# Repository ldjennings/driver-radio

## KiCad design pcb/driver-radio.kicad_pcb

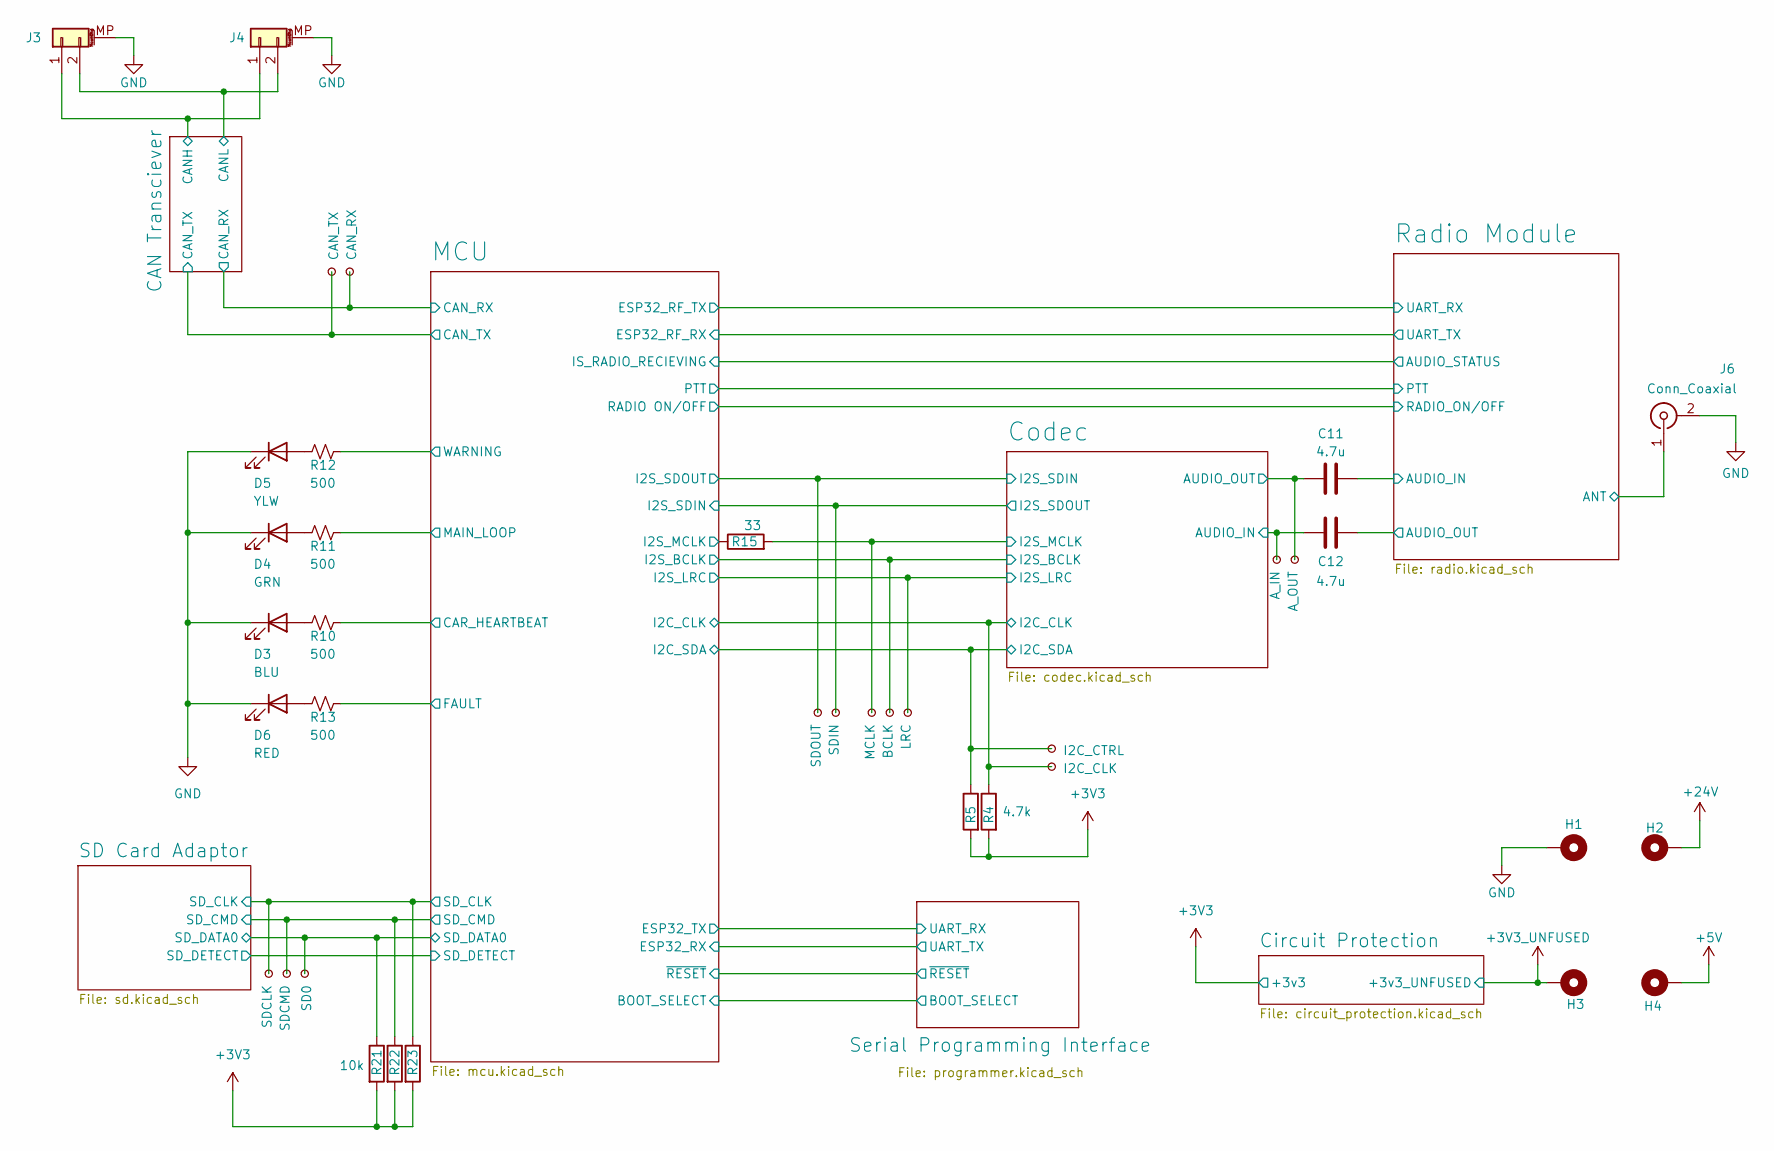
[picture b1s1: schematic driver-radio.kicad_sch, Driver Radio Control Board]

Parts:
C11, C12: 4.7u; C_0805_2012Metric
D3: BLU; LED_0402_1005Metric
D4: GRN; LED_0402_1005Metric
D5: YLW; LED_0402_1005Metric
D6: RED; LED_0402_1005Metric
H1, H2, H3, H4: MountingHole_Pad; glv_mainboard_hole
J3, J4: Conn_01x02_MountingPin; JST_GH_SM02B-GHS-TB_1x02-1MP_P1.25mm_Horizontal
J6: Conn_Coaxial; SMA_Molex_73251-1153_EdgeMount_Horizontal
R4, R5: 4.7k; R_0402_1005Metric
R10, R11, R12, R13: 500; R_0402_1005Metric
R15: 33; R_0402_1005Metric
R21, R22, R23: 10k; R_0402_1005Metric_Pad0.72x0.64mm_HandSolder
TP1: CAN_TX; tp-ev24-nobacksilk
TP2: CAN_RX; tp-ev24-nobacksilk
TP3: I2C_CTRL; tp-ev24-nobacksilk
TP4: I2C_CLK; tp-ev24-nobacksilk
TP5: MCLK; tp-ev24-nobacksilk
TP6: LRC; tp-ev24-nobacksilk
TP7: BCLK; tp-ev24-nobacksilk
TP8: SDIN; tp-ev24-nobacksilk
TP9: SDOUT; tp-ev24-nobacksilk
TP10: A_OUT; tp-ev24-nobacksilk
TP11: A_IN; tp-ev24-nobacksilk
TP12: SD0; tp-ev24-nobacksilk
TP16: SDCLK; tp-ev24-nobacksilk
TP17: SDCMD; tp-ev24-nobacksilk

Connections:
+3V3: R4.2, R5.2, R21.2, R22.2, R23.2; also elsewhere on the board
+3V3_UNFUSED: H3.1; also elsewhere on the board
+5V: H4.1; also elsewhere on the board
+24V: H2.1
/CAN Transciever/CANH: J3.1, J4.1; also elsewhere on the board
/CAN Transciever/CANL: J3.2, J4.2; also elsewhere on the board
/CAN Transciever/CAN_RX: TP2.1; also elsewhere on the board
/CAN Transciever/CAN_TX: TP1.1; also elsewhere on the board
/Codec/AUDIO_IN: C12.2, TP11.1; also elsewhere on the board
/Codec/AUDIO_OUT: C11.2, TP10.1; also elsewhere on the board
/Codec/I2C_CLK: R4.1, TP4.1; also elsewhere on the board
/Codec/I2C_SDA: R5.1, TP3.1; also elsewhere on the board
/Codec/I2S_BCLK: TP7.1; also elsewhere on the board
/Codec/I2S_LRC: TP6.1; also elsewhere on the board
/Codec/I2S_MCLK: R15.2, TP5.1; also elsewhere on the board
/Codec/I2S_SDIN: TP9.1; also elsewhere on the board
/Codec/I2S_SDOUT: TP8.1; also elsewhere on the board
/MCU/BOOT_SELECT: R15.1; also elsewhere on the board
/MCU/CAR_HEARTBEAT: R10.1; also elsewhere on the board
/MCU/FAULT: R13.1; also elsewhere on the board
/MCU/MAIN_LOOP: R11.1; also elsewhere on the board
/MCU/SD_CLK: R23.1, TP16.1; also elsewhere on the board
/MCU/SD_CMD: R22.1, TP17.1; also elsewhere on the board
/MCU/SD_DATA0: R21.1, TP12.1; also elsewhere on the board
/MCU/WARNING: R12.1; also elsewhere on the board
/Radio Module/ANT: J6.1 (In); also elsewhere on the board
/Radio Module/AUDIO_IN: C11.1; also elsewhere on the board
/Radio Module/AUDIO_OUT: C12.1; also elsewhere on the board
GND: D3.1 (K), D4.1 (K), D5.1 (K), D6.1 (K), H1.1, J3.MP (MountPin), J4.MP (MountPin), J6.2 (Ext); also elsewhere on the board
unnamed: D3.2 (A), R10.2
unnamed: D4.2 (A), R11.2
unnamed: D5.2 (A), R12.2
unnamed: D6.2 (A), R13.2

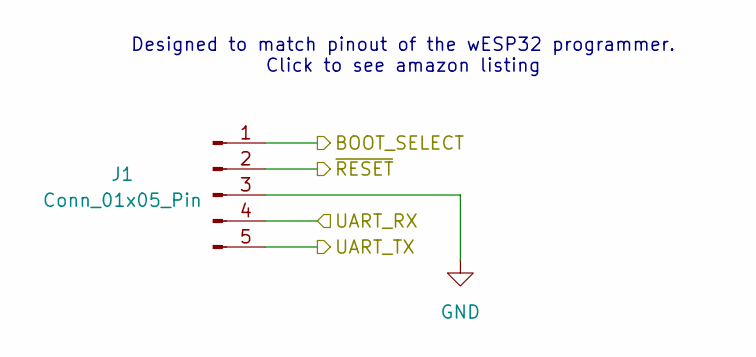
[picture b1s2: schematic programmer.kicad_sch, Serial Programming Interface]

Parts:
J1: Conn_01x05_Pin; PinHeader_1x05_P2.54mm_Vertical

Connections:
/MCU/BOOT_SELECT: J1.1; also elsewhere on the board
/MCU/ESP32_RX: J1.5; also elsewhere on the board
/MCU/ESP32_TX: J1.4; also elsewhere on the board
/MCU/~RESET: J1.2; also elsewhere on the board
GND: J1.3; also elsewhere on the board

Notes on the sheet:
Designed to match pinout of the wESP32 programmer. Click to see amazon listing

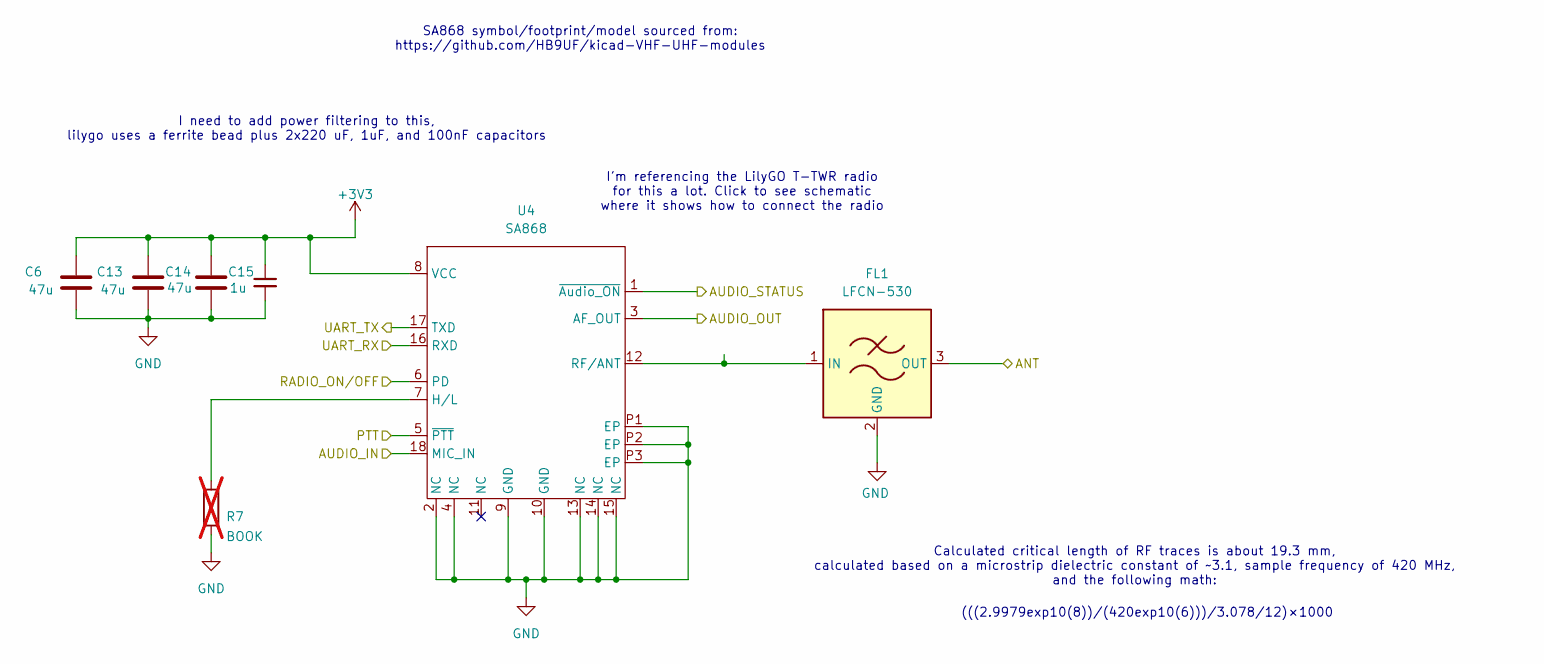
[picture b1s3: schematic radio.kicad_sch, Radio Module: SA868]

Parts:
C6, C13, C14: 47u; C_1206_3216Metric
C15: 1u; C_0402_1005Metric
FL1: LFCN-530; Filter_Mini-Circuits_FV1206
R7: BOOK; R_0402_1005Metric; not fitted
U4: SA868; VHF_UHF_Module_generic

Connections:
+3V3: C6.1, C13.1, C14.1, C15.1, U4.8 (VCC); also elsewhere on the board
/MCU/ESP32_RF_RX: U4.17 (TXD); also elsewhere on the board
/MCU/ESP32_RF_TX: U4.16 (RXD); also elsewhere on the board
/MCU/IS_RADIO_RECIEVING: U4.1 (~Audio_ON); also elsewhere on the board
/MCU/PTT: U4.5 (~PTT); also elsewhere on the board
/MCU/RADIO ON/OFF: U4.6 (PD); also elsewhere on the board
/Radio Module/ANT: FL1.3 (OUT); also elsewhere on the board
/Radio Module/AUDIO_IN: U4.18 (MIC_IN); also elsewhere on the board
/Radio Module/AUDIO_OUT: U4.3 (AF_OUT); also elsewhere on the board
GND: C6.2, C13.2, C14.2, C15.2, FL1.2 (GND), FL1.4 (GND), R7.1, U4.2 (NC), U4.4 (NC), U4.9 (GND), U4.10 (GND), U4.13 (NC), U4.14 (NC), U4.15 (NC), U4.P1 (EP), U4.P2 (EP), U4.P3 (EP); also elsewhere on the board
unnamed: FL1.1 (IN), U4.12 (RF/ANT)
unnamed: R7.2, U4.7 (H/L)

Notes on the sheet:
I'm referencing the LilyGO T-TWR radio for this a lot. Click to see schematic where it shows how to connect the radio
SA868 symbol/footprint/model sourced from: https://github.com/HB9UF/kicad-VHF-UHF-modules
I need to add power filtering to this, lilygo uses a ferrite bead plus 2x220 uF, 1uF, and 100nF capacitors
Calculated critical length of RF traces is about 19.3 mm, calculated based on a microstrip dielectric constant of ~3.1, sample frequency of 420 MHz, and the following math:
(((2.9979exp10(8))/(420exp10(6)))/3.078/12)×1000

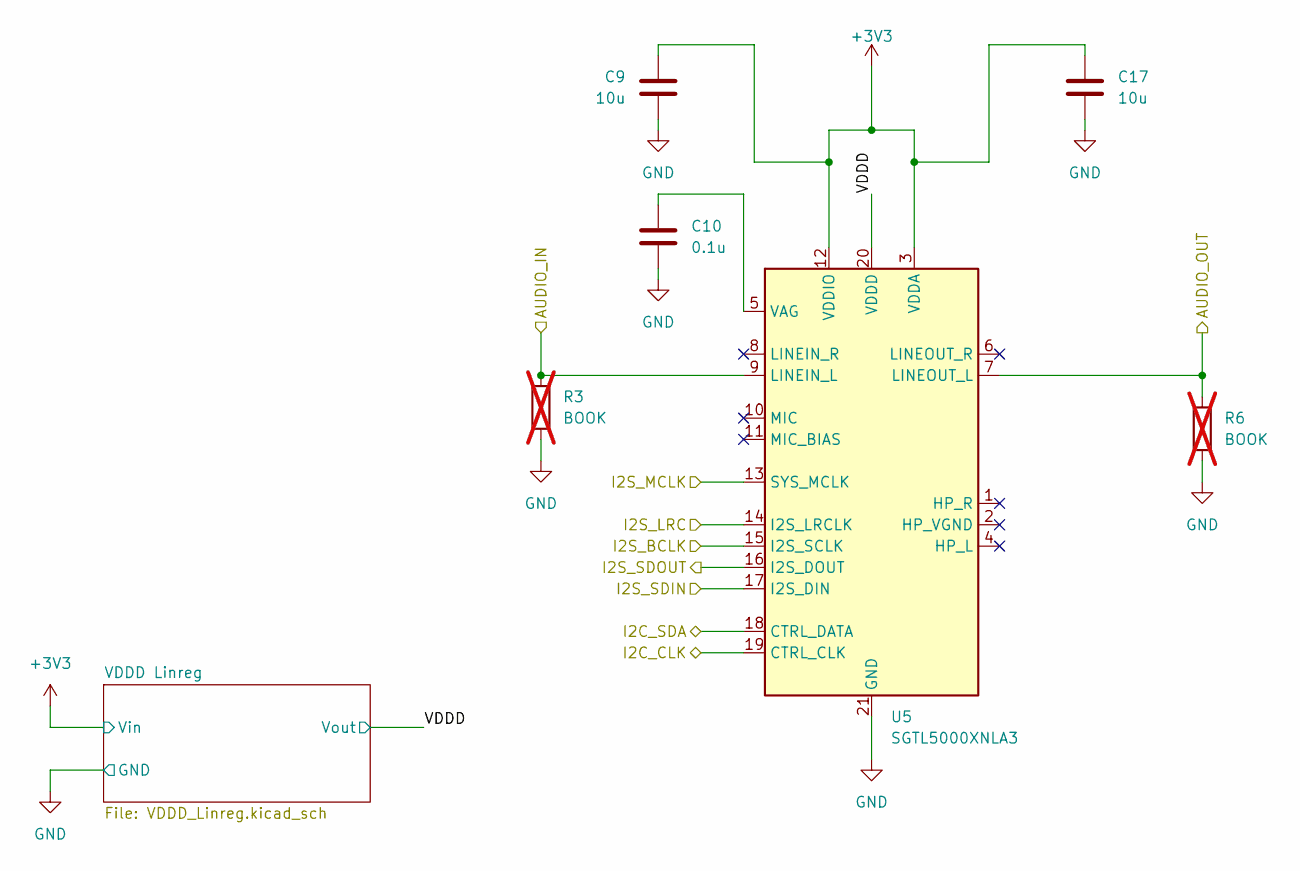
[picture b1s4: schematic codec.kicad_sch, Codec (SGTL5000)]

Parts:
C9, C17: 10u; C_0402_1005Metric
C10: 0.1u; C_0402_1005Metric
R3, R6: BOOK; R_0402_1005Metric; not fitted
U5: SGTL5000XNLA3; QFN-20-1EP_3x3mm_P0.4mm_EP1.65x1.65mm

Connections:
+3V3: C9.1, C17.1, U5.3 (VDDA), U5.12 (VDDIO); also elsewhere on the board
/Codec/AUDIO_IN: R3.2, U5.9 (LINEIN_L); also elsewhere on the board
/Codec/AUDIO_OUT: R6.2, U5.7 (LINEOUT_L); also elsewhere on the board
/Codec/I2C_CLK: U5.19 (CTRL_CLK); also elsewhere on the board
/Codec/I2C_SDA: U5.18 (CTRL_DATA); also elsewhere on the board
/Codec/I2S_BCLK: U5.15 (I2S_SCLK); also elsewhere on the board
/Codec/I2S_LRC: U5.14 (I2S_LRCLK); also elsewhere on the board
/Codec/I2S_MCLK: U5.13 (SYS_MCLK); also elsewhere on the board
/Codec/I2S_SDIN: U5.17 (I2S_DIN); also elsewhere on the board
/Codec/I2S_SDOUT: U5.16 (I2S_DOUT); also elsewhere on the board
/Codec/VDDD: U5.20 (VDDD); also elsewhere on the board
GND: C9.2, C10.2, C17.2, R3.1, R6.1, U5.21 (GND); also elsewhere on the board
unnamed: C10.1, U5.5 (VAG)

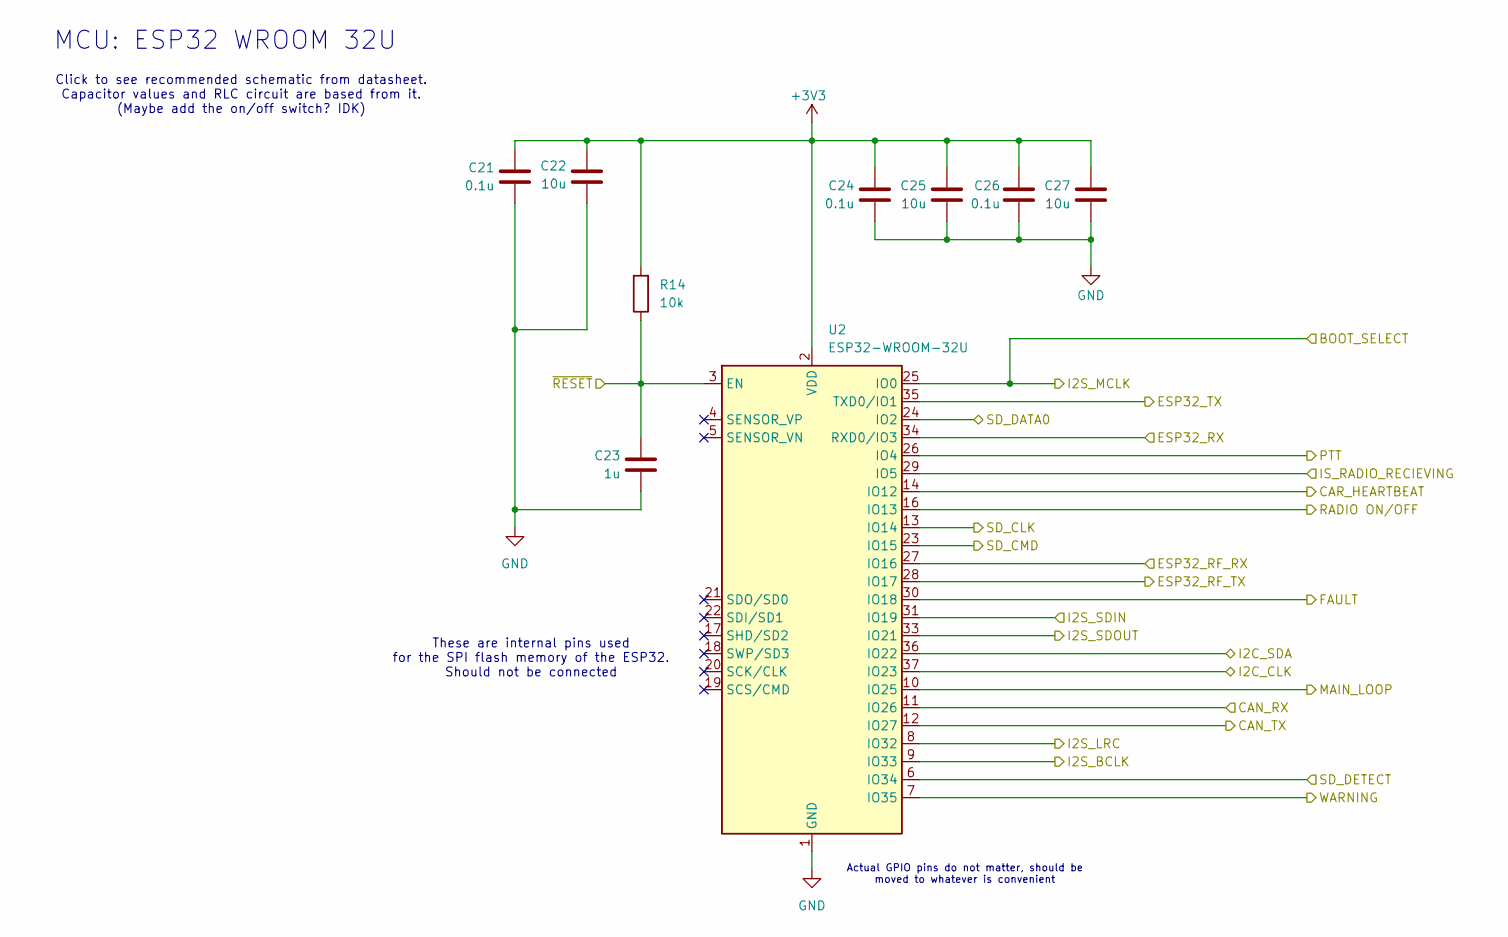
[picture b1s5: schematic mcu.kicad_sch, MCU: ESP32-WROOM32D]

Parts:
C21, C24, C26: 0.1u; C_0402_1005Metric
C22, C25, C27: 10u; C_0402_1005Metric
C23: 1u; C_0402_1005Metric
R14: 10k; R_0402_1005Metric
U2: ESP32-WROOM-32U

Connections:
+3V3: C21.1, C22.1, C24.1, C25.1, C26.1, C27.1, R14.2, U2.2 (VDD); also elsewhere on the board
/CAN Transciever/CAN_RX: U2.11 (IO26); also elsewhere on the board
/CAN Transciever/CAN_TX: U2.12 (IO27); also elsewhere on the board
/Codec/I2C_CLK: U2.37 (IO23); also elsewhere on the board
/Codec/I2C_SDA: U2.36 (IO22); also elsewhere on the board
/Codec/I2S_BCLK: U2.9 (IO33); also elsewhere on the board
/Codec/I2S_LRC: U2.8 (IO32); also elsewhere on the board
/Codec/I2S_SDIN: U2.33 (IO21); also elsewhere on the board
/Codec/I2S_SDOUT: U2.31 (IO19); also elsewhere on the board
/MCU/BOOT_SELECT: U2.25 (IO0); also elsewhere on the board
/MCU/CAR_HEARTBEAT: U2.14 (IO12); also elsewhere on the board
/MCU/ESP32_RF_RX: U2.27 (IO16); also elsewhere on the board
/MCU/ESP32_RF_TX: U2.28 (IO17); also elsewhere on the board
/MCU/ESP32_RX: U2.34 (RXD0/IO3); also elsewhere on the board
/MCU/ESP32_TX: U2.35 (TXD0/IO1); also elsewhere on the board
/MCU/FAULT: U2.30 (IO18); also elsewhere on the board
/MCU/IS_RADIO_RECIEVING: U2.29 (IO5); also elsewhere on the board
/MCU/MAIN_LOOP: U2.10 (IO25); also elsewhere on the board
/MCU/PTT: U2.26 (IO4); also elsewhere on the board
/MCU/RADIO ON/OFF: U2.16 (IO13); also elsewhere on the board
/MCU/SD_CLK: U2.13 (IO14); also elsewhere on the board
/MCU/SD_CMD: U2.23 (IO15); also elsewhere on the board
/MCU/SD_DATA0: U2.24 (IO2); also elsewhere on the board
/MCU/SD_DETECT: U2.6 (IO34); also elsewhere on the board
/MCU/WARNING: U2.7 (IO35); also elsewhere on the board
/MCU/~RESET: C23.2, R14.1, U2.3 (EN); also elsewhere on the board
GND: C21.2, C22.2, C23.1, C24.2, C25.2, C26.2, C27.2, U2.1 (GND), U2.15 (GND), U2.38 (GND), U2.39 (GND); also elsewhere on the board

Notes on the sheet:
Actual GPIO pins do not matter, should be moved to whatever is convenient
Click to see recommended schematic from datasheet. Capacitor values and RLC circuit are based from it. (Maybe add the on/off switch? IDK)
These are internal pins used for the SPI flash memory of the ESP32. Should not be connected
MCU: ESP32 WROOM 32U

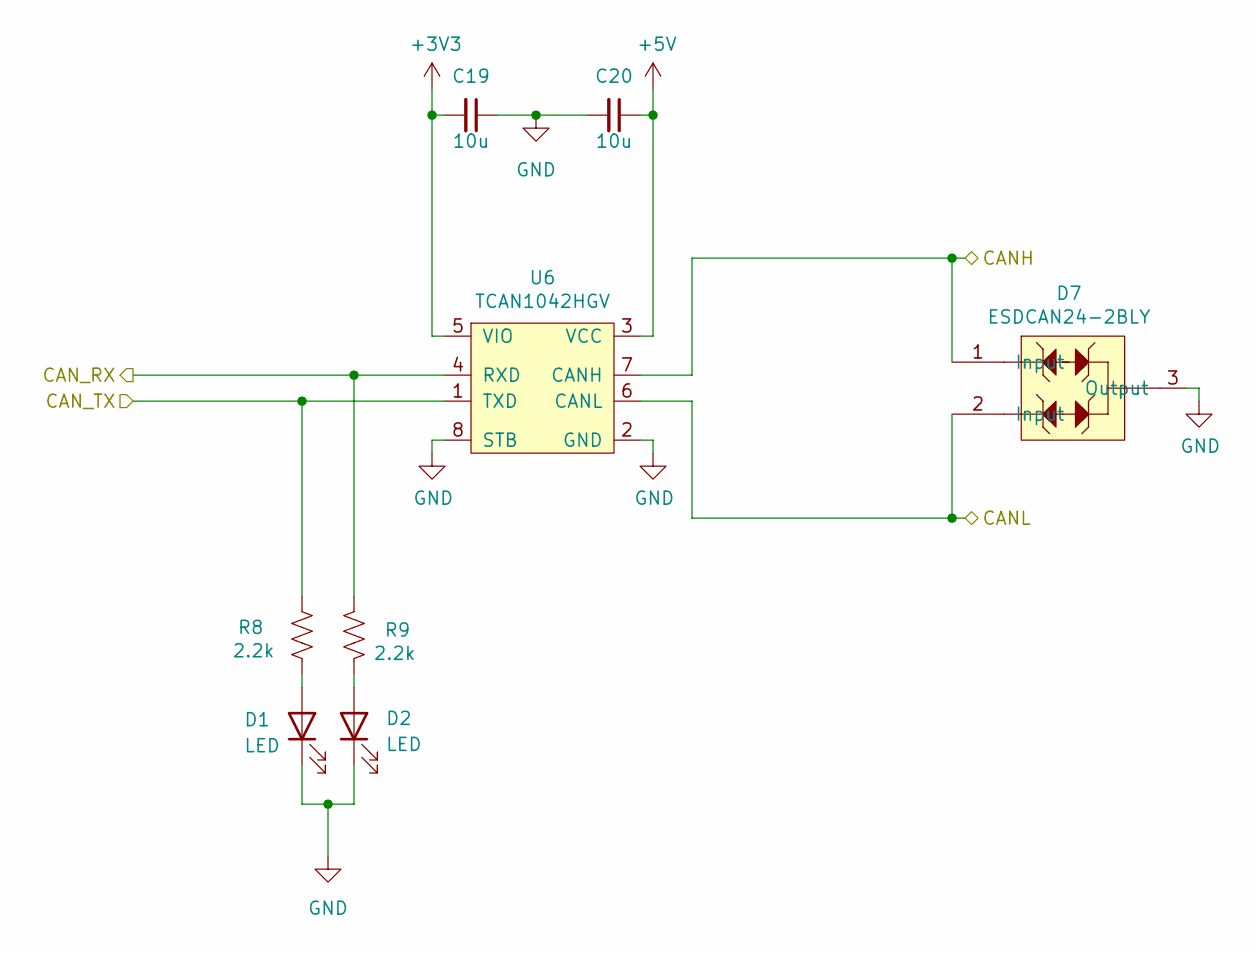
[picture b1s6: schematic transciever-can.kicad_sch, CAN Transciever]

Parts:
C19, C20: 10u; C_0402_1005Metric
D1, D2: LED; LED_0402_1005Metric
D7: ESDCAN24-2BLY; SOT-23-3
R8, R9: 2.2k; R_0402_1005Metric
U6: TCAN1042HGV; SOIC-8_3.9x4.9mm_P1.27mm

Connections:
+3V3: C19.2, U6.5 (VIO); also elsewhere on the board
+5V: C20.1, U6.3 (VCC); also elsewhere on the board
/CAN Transciever/CANH: D7.1 (Input), U6.7 (CANH); also elsewhere on the board
/CAN Transciever/CANL: D7.2 (Input), U6.6 (CANL); also elsewhere on the board
/CAN Transciever/CAN_RX: R9.1, U6.4 (RXD); also elsewhere on the board
/CAN Transciever/CAN_TX: R8.1, U6.1 (TXD); also elsewhere on the board
GND: C19.1, C20.2, D1.1 (K), D2.1 (K), D7.3 (Output), U6.2 (GND), U6.8 (STB); also elsewhere on the board
unnamed: D1.2 (A), R8.2
unnamed: D2.2 (A), R9.2

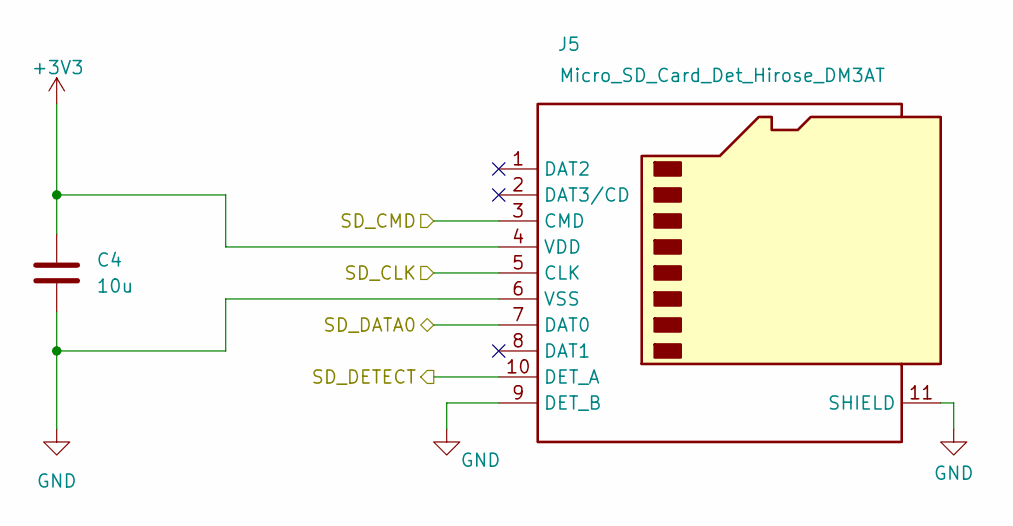
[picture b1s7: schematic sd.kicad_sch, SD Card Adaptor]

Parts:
C4: 10u; C_0402_1005Metric
J5: Micro_SD_Card_Det_Hirose_DM3AT; microSD_HC_Hirose_DM3BT-DSF-PEJS

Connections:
+3V3: C4.1, J5.4 (VDD); also elsewhere on the board
/MCU/SD_CLK: J5.5 (CLK); also elsewhere on the board
/MCU/SD_CMD: J5.3 (CMD); also elsewhere on the board
/MCU/SD_DATA0: J5.7 (DAT0); also elsewhere on the board
/MCU/SD_DETECT: J5.10 (DET_A); also elsewhere on the board
GND: C4.2, J5.6 (VSS), J5.9 (DET_B), J5.11 (SHIELD); also elsewhere on the board

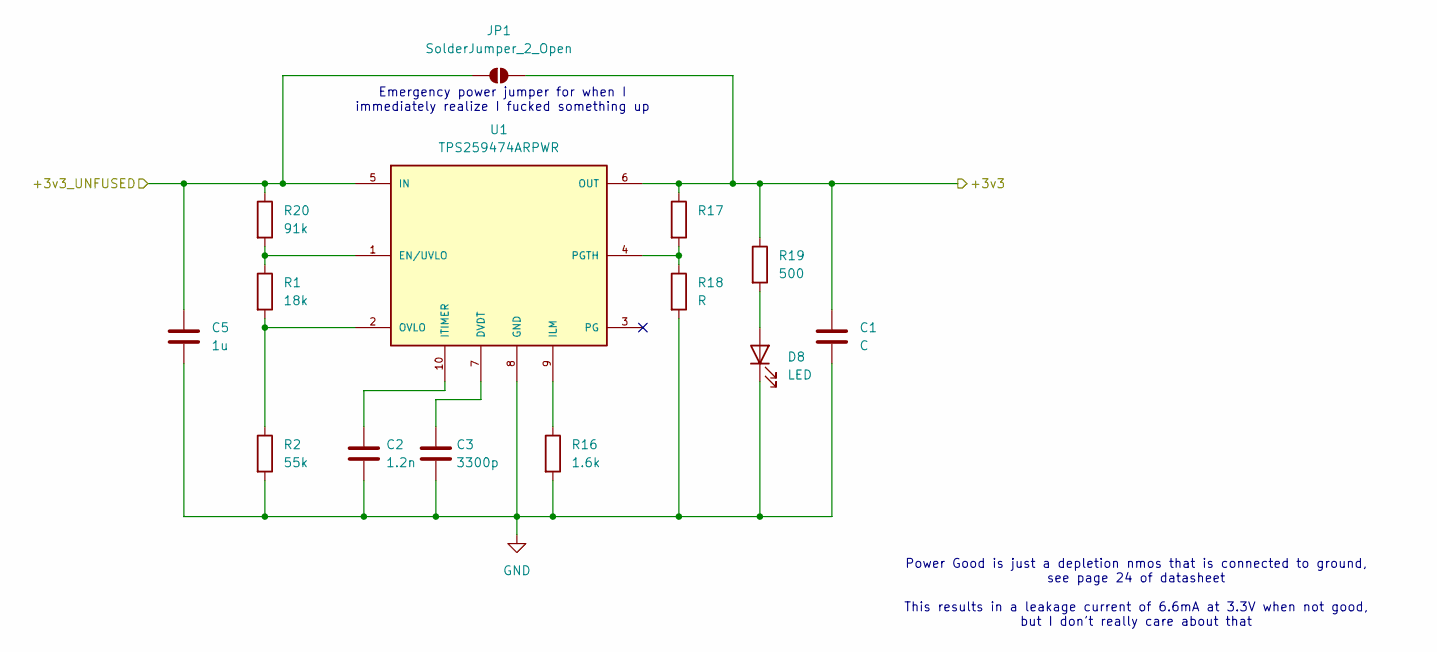
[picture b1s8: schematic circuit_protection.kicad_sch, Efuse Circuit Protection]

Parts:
C1: C; C_0402_1005Metric
C2: 1.2n; C_0402_1005Metric
C3: 3300p; C_0402_1005Metric
C5: 1u; C_0402_1005Metric
D8: LED; D_0402_1005Metric
JP1: SolderJumper_2_Open; SolderJumper-2_P1.3mm_Open_RoundedPad1.0x1.5mm
R1: 18k; R_0402_1005Metric
R2: 55k; R_0402_1005Metric
R16: 1.6k; R_0402_1005Metric
R17: R_0402_1005Metric
R18: R; R_0402_1005Metric
R19: 500; R_0402_1005Metric
R20: 91k; R_0402_1005Metric
U1: TPS259474ARPWR; IC_TPS259474ARPWR; PARTREV A

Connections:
+3V3: C1.1, JP1.2 (B), R17.1, R19.1, U1.6 (OUT); also elsewhere on the board
+3V3_UNFUSED: C5.1, JP1.1 (A), R20.1, U1.5 (IN); also elsewhere on the board
GND: C1.2, C2.2, C3.2, C5.2, D8.1 (K), R2.2, R16.2, R18.2, U1.8 (GND); also elsewhere on the board
unnamed: D8.2 (A), R19.2
unnamed: C3.1, U1.7 (DVDT)
unnamed: R1.1, R20.2, U1.1 (EN/UVLO)
unnamed: R16.1, U1.9 (ILM)
unnamed: C2.1, U1.10 (ITIMER)
unnamed: R1.2, R2.1, U1.2 (OVLO)
unnamed: R17.2, R18.1, U1.4 (PGTH)

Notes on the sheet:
Power Good is just a depletion nmos that is connected to ground, see page 24 of datasheet This results in a leakage current of 6.6mA at 3.3V when not good, but I don't really care about that
Emergency power jumper for when I immediately realize I fucked something up

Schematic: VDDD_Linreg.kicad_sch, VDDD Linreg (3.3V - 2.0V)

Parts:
C8: 0.1u; C_0402_1005Metric
C18: 4.7u; C_0402_1005Metric
U3: TLV70220PDBVR; SOT-23-5

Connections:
+3V3: C8.1, U3.1 (IN), U3.3 (EN); also elsewhere on the board
/Codec/VDDD: C18.1, U3.5 (OUT); also elsewhere on the board
GND: C8.2, C18.2, U3.2 (GND); also elsewhere on the board

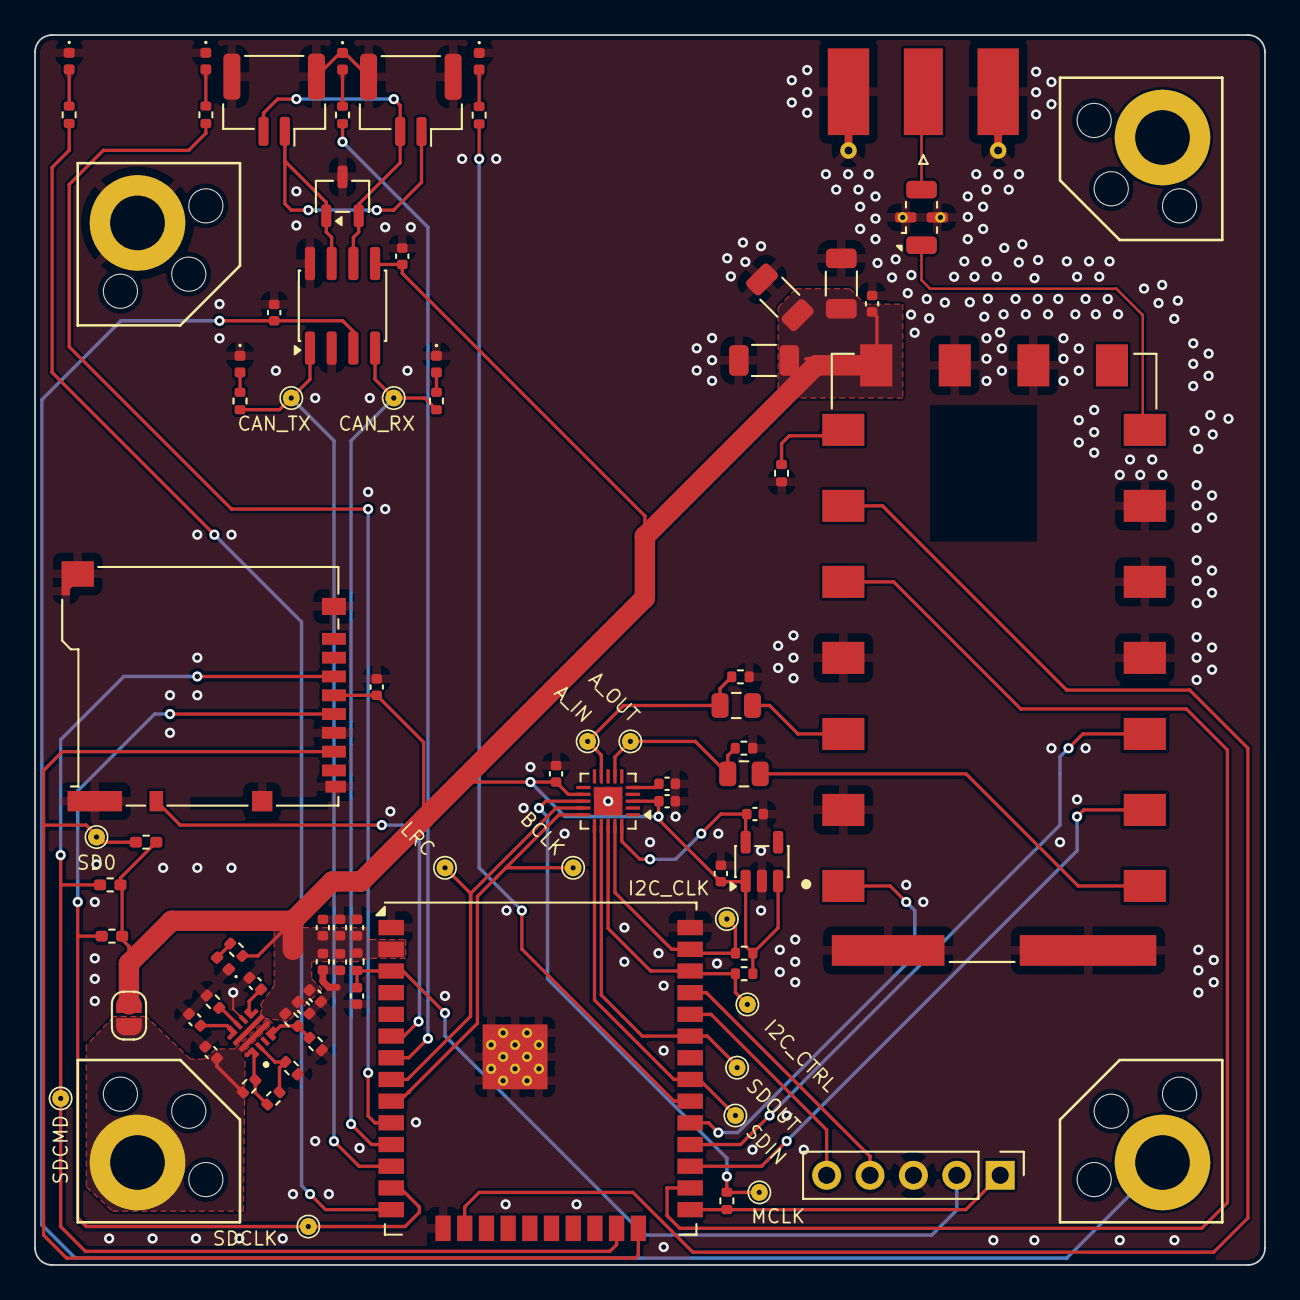
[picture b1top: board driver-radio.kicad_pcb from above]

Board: 4 copper layers, 72.0 x 72.0 mm, 87 parts (0 on the bottom side), 54 nets.

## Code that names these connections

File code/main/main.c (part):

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
// #include "funky.h"

#define I2S_SDOUT                       GPIO_NUM_25                 /*!< GPIO number used for I2S Serial Data Output*/
#define I2S_SDIN                        GPIO_NUM_26                 /*!< GPIO number used for I2S Serial Data Input */
#define I2S_BCLK                        GPIO_NUM_27                 /*!< GPIO number used for I2S Serial Clock      */
#define I2S_LRCLK                       GPIO_NUM_14                 /*!< GPIO number used for I2S Left/Right Clock  */
#define I2S_MCLK                        GPIO_NUM_0                  /*!< GPIO number used for I2S Master Clock      */

#define I2C_MASTER_SCL_IO               GPIO_NUM_32                 /*!< GPIO number used for I2C master clock      */
#define I2C_MASTER_SDA_IO               GPIO_NUM_33                 /*!< GPIO number used for I2C master data       */
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
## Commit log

2025-06-10 spice stuff
2025-06-10 added code
2025-06-10 added bom to gitignore
2025-06-10 Changed flake to actually be a flake, added direnv
2025-08-28 Merging in work from FSAE repo from when I forgot this one existed
2025-10-05 Quite a few changes
2026-01-05 Removed baofeng outline
2026-01-05 starting to make flake for whole project
2026-05-05 reworked flake
2026-05-05 got proper model imported
2026-05-05 updated footprints
2026-05-05 added 3d model
